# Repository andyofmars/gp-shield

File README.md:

# gp-shield
## A general purpose arduino-compatible shield for UTAS projects

## Overview
The shield is intended to be used as a general purpose shield for Arduino Uno compatible microcontroller development boards or as an interface between a development board and other custom electronics.

From previous projects we have identified multiple common issues when interfacing with common microcontroller development boards including the Arduino UNO and Xplained Mini series of development boards.
- Many development boards are sensitive to fluctuations in the power supply during programming and can become 'bricked'.
- A lack of protection on the Vin and 5V lines when being powered from a shield or other electronics makes them susceptible to damage.
- Due to the lack of protection and the large number of exposed GPIO pins it is easy to draw too much current or apply an overvoltage condition which will damage the microcontroller.

**See [Rugged Circuits](https://www.rugged-circuits.com/10-ways-to-destroy-an-arduino) for more detail on common issues with the Arduino UNO.**

To resolve these issue for most use cases and provide general functionality commonly needed in electronics projects we have developed the gp-shield to be used as the standard method of interfacing with Arduino UNO compatible development boards.

## Features
- Can be powered from external battery (~6V - 20V)
- On-board power supply with overvoltage (25V?), overcurrent (6A), and reverse polarity protection as well as adjustable undervoltage lockout and an on-board or external power switch.
- Onboard 5V regulation (up to 1A output) with circuitry with a jumper to isolate 5V from the development board.
- Overvoltage (~5.1V) and overcurrent (~30mA) protection on all GPIO pins when using the on-board headers and connectors.
- ICD style analogue outputs, PORTD and PORTB GPIO pins, 6 servo-style PWM outputs, UART, SPI and a high current output for powereing other electronics from the same supply with all of the built in seafty features.
- On-board microcontroller reset button
- On-board general purpose LED and push button

The board itself is 2-layers with double-sided load. All components use footprints suitable for hand-soldering. It is intended to be assembled in-house using pick-and-place machine and reflow soldering.

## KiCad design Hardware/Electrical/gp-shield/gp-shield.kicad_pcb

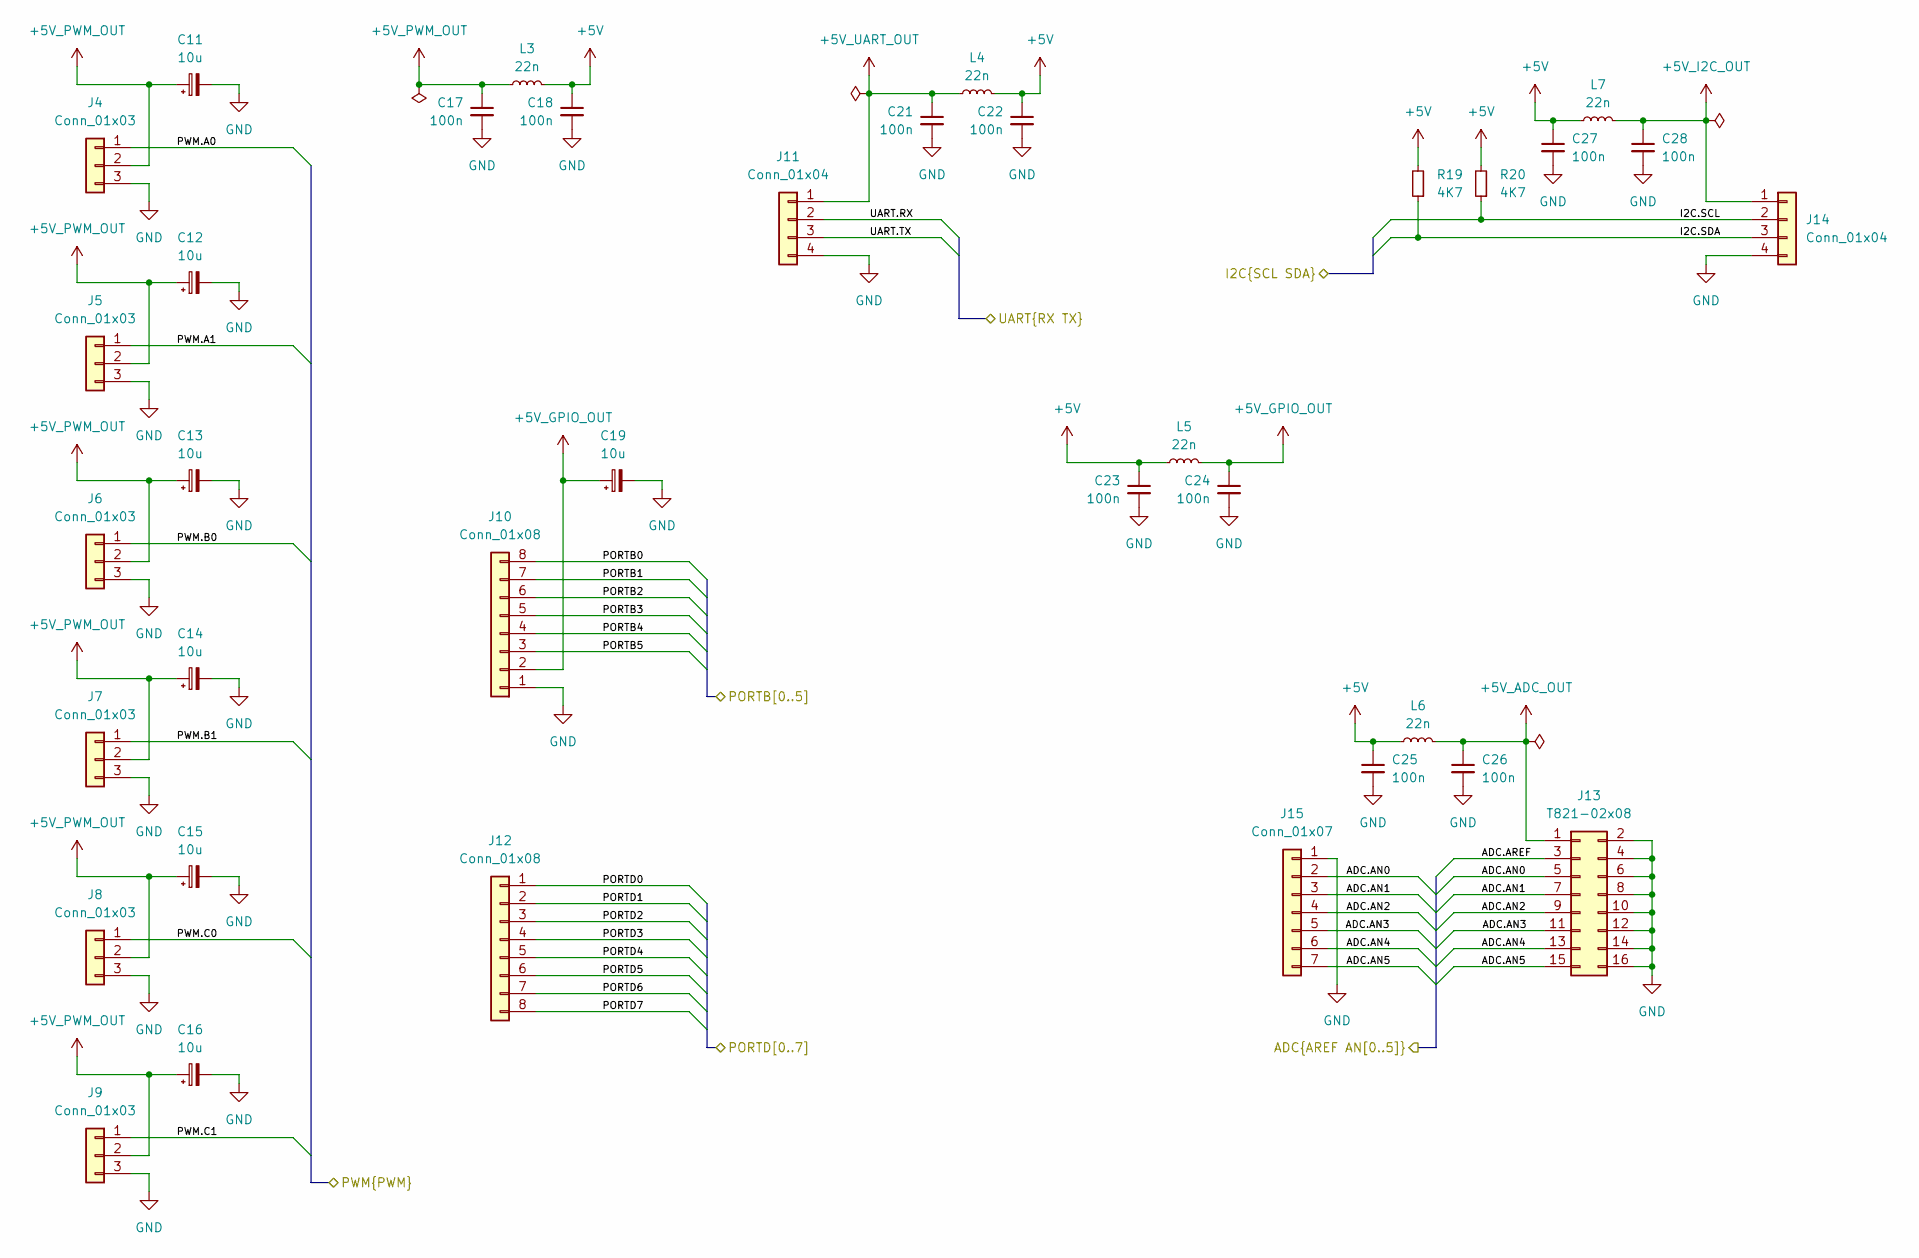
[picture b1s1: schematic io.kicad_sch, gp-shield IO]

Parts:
C11, C12, C13, C14, C15, C16, C19: 10u; C_0805_2012Metric_Pad1.18x1.45mm_HandSolder
C17, C18, C21, C22, C23, C24, C25, C26, C27, C28: 100n; C_0805_2012Metric_Pad1.18x1.45mm_HandSolder
J4, J5, J6, J7, J8, J9: Conn_01x03; PinHeader_1x03_P2.54mm_Vertical
J10, J12: Conn_01x08; PinSocket_1x08_P2.54mm_Vertical
J11, J14: Conn_01x04; Molex_KK-254_AE-6410-04A_1x04_P2.54mm_Vertical
J13: T821-02x08; IDC-Header_2x08_P2.54mm_Horizontal
J15: Conn_01x07; PinSocket_1x07_P2.54mm_Vertical
L3, L4, L5, L6, L7: 22n; L_0805_2012Metric_Pad1.15x1.40mm_HandSolder
R19, R20: 4K7; R_0805_2012Metric_Pad1.20x1.40mm_HandSolder

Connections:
+5V: C18.1, C22.1, C23.1, C25.1, C27.1, L3.1, L4.1, L5.2, L6.1, L7.1, R19.2, R20.2; also elsewhere on the board
+5V_ADC_OUT: C26.1, J13.1, L6.2
+5V_GPIO_OUT: C19.1, C24.1, J10.2, L5.1
+5V_I2C_OUT: C28.1, J14.1, L7.2
+5V_PWM_OUT: C11.1, C12.1, C13.1, C14.1, C15.1, C16.1, C17.1, J4.2, J5.2, J6.2, J7.2, J8.2, J9.2, L3.2
+5V_UART_OUT: C21.1, J11.1, L4.2
/IO/ADC.AN0: J13.5, J15.2; also elsewhere on the board
/IO/ADC.AN1: J13.7, J15.3; also elsewhere on the board
/IO/ADC.AN2: J13.9, J15.4; also elsewhere on the board
/IO/ADC.AN3: J13.11, J15.5; also elsewhere on the board
/IO/ADC.AN4: J13.13, J15.6; also elsewhere on the board
/IO/ADC.AN5: J13.15, J15.7; also elsewhere on the board
/IO/ADC.AREF: J13.3; also elsewhere on the board
/IO/I2C.SCL: J14.2, R20.1; also elsewhere on the board
/IO/I2C.SDA: J14.3, R19.1; also elsewhere on the board
/IO/PORTB0: J10.8; also elsewhere on the board
/IO/PORTB1: J10.7; also elsewhere on the board
/IO/PORTB2: J10.6; also elsewhere on the board
/IO/PORTB3: J10.5; also elsewhere on the board
/IO/PORTB4: J10.4; also elsewhere on the board
/IO/PORTB5: J10.3; also elsewhere on the board
/IO/PORTD0: J12.1; also elsewhere on the board
/IO/PORTD1: J12.2; also elsewhere on the board
/IO/PORTD2: J12.3; also elsewhere on the board
/IO/PORTD3: J12.4; also elsewhere on the board
/IO/PORTD4: J12.5; also elsewhere on the board
/IO/PORTD5: J12.6; also elsewhere on the board
/IO/PORTD6: J12.7; also elsewhere on the board
/IO/PORTD7: J12.8; also elsewhere on the board
/IO/PWM.A0: J4.1; also elsewhere on the board
/IO/PWM.A1: J5.1; also elsewhere on the board
/IO/PWM.B0: J6.1; also elsewhere on the board
/IO/PWM.B1: J7.1; also elsewhere on the board
/IO/PWM.C0: J8.1; also elsewhere on the board
/IO/PWM.C1: J9.1; also elsewhere on the board
/IO/UART.RX: J11.2; also elsewhere on the board
/IO/UART.TX: J11.3; also elsewhere on the board
GND: C11.2, C12.2, C13.2, C14.2, C15.2, C16.2, C17.2, C18.2, C19.2, C21.2, C22.2, C23.2, C24.2, C25.2, C26.2, C27.2, C28.2, J4.3, J5.3, J6.3, J7.3, J8.3, J9.3, J10.1, J11.4, J13.2, J13.4, J13.6, J13.8, J13.10, J13.12, J13.14, J13.16, J14.4, J15.1; also elsewhere on the board

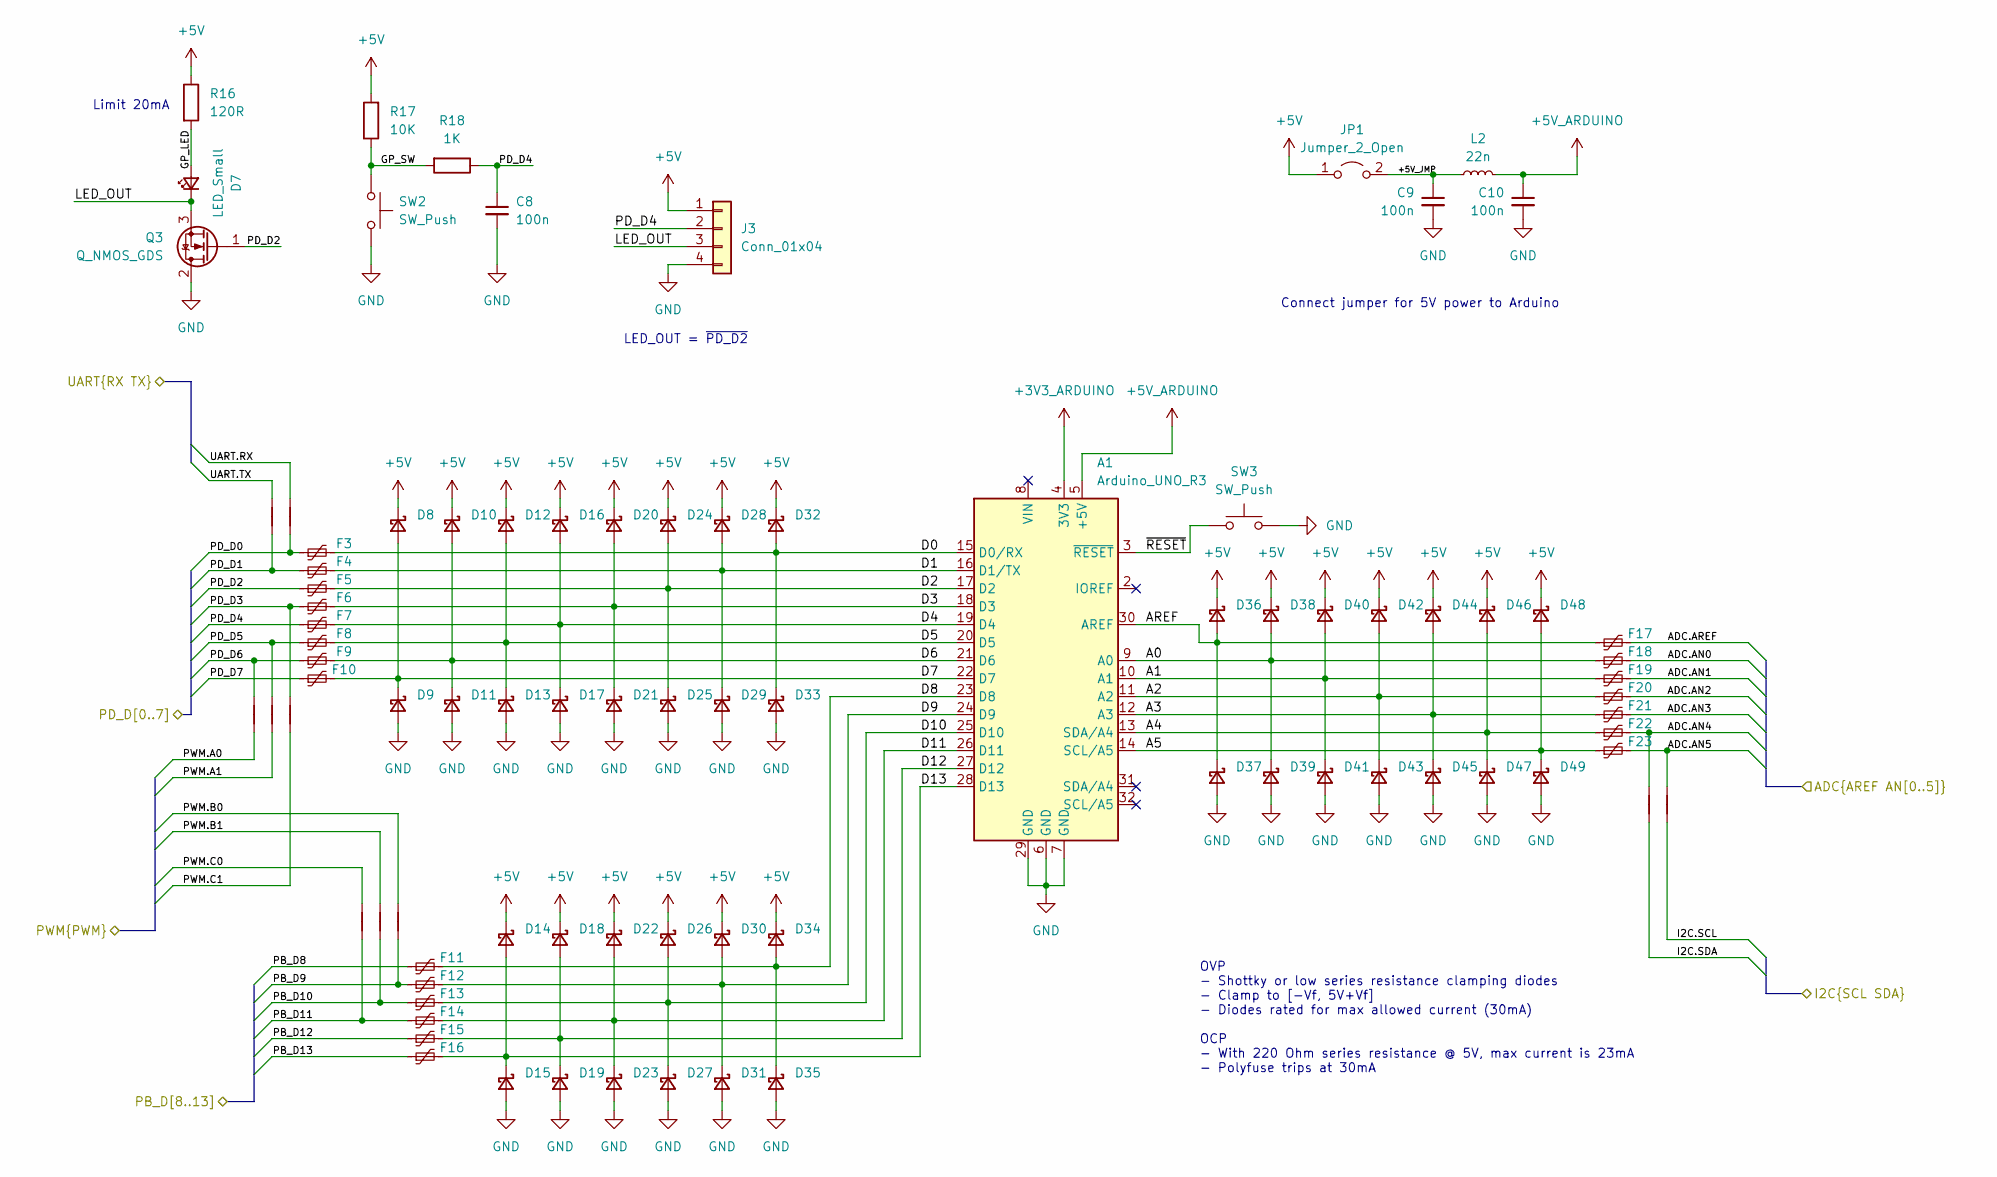
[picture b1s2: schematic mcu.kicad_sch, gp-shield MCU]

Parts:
A1: Arduino_UNO_R3
C8, C9, C10: 100n; C_0805_2012Metric_Pad1.18x1.45mm_HandSolder
D7: LED_Small; LED_0805_2012Metric_Pad1.15x1.40mm_HandSolder
D8, D9, D10, D11, D12, D13, D14, D15, D16, D17, D18, D19, D20, D21, D22, D23, D24, D25, D26, D27, D28, D29, D30, D31, D32, D33, D34, D35, D36, D37, D38, D39, D40, D41, D42, D43, D44, D45, D46, D47, D48, D49: D_Schottky_Small; D_0805_2012Metric_Pad1.15x1.40mm_HandSolder
F3, F4, F5, F6, F7, F8, F9, F10, F11, F12, F13, F14, F15, F16, F17, F18, F19, F20, F21, F22, F23: Polyfuse_Small; Fuse_0805_2012Metric_Pad1.15x1.40mm_HandSolder; Digikey Part No PRG18BB221MB1RB
J3: Conn_01x04; Molex_KK-254_AE-6410-04A_1x04_P2.54mm_Vertical
JP1: Jumper_2_Open; PinHeader_1x02_P2.54mm_Vertical
L2: 22n; L_0805_2012Metric_Pad1.15x1.40mm_HandSolder
NT1, NT2, NT3, NT4, NT5, NT6, NT7, NT8, NT9, NT10: NetTie_2; NetTie-2_THT_Pad0.3mm
Q3: Q_NMOS_GDS; SOT-23
R16: 120R; R_0805_2012Metric_Pad1.20x1.40mm_HandSolder
R17: 10K; R_0805_2012Metric_Pad1.20x1.40mm_HandSolder
R18: 1K; R_0805_2012Metric_Pad1.20x1.40mm_HandSolder
SW2, SW3: SW_Push; SW_TH_Tactile_Omron_B3F-10xx

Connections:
+3V3_ARDUINO: A1.4 (3V3)
+5V: D8.1 (K), D10.1 (K), D12.1 (K), D14.1 (K), D16.1 (K), D18.1 (K), D20.1 (K), D22.1 (K), D24.1 (K), D26.1 (K), D28.1 (K), D30.1 (K), D32.1 (K), D34.1 (K), D36.1 (K), D38.1 (K), D40.1 (K), D42.1 (K), D44.1 (K), D46.1 (K), D48.1 (K), J3.1, JP1.1 (A), R16.1, R17.2; also elsewhere on the board
+5V_ARDUINO: A1.5 (+5V), C10.1, L2.1
/IO/ADC.AN0: F18.2; also elsewhere on the board
/IO/ADC.AN1: F19.2; also elsewhere on the board
/IO/ADC.AN2: F20.2; also elsewhere on the board
/IO/ADC.AN3: F21.2; also elsewhere on the board
/IO/ADC.AN4: F22.2, NT9.2; also elsewhere on the board
/IO/ADC.AN5: F23.2, NT10.2; also elsewhere on the board
/IO/ADC.AREF: F17.2; also elsewhere on the board
/IO/I2C.SCL: NT10.1; also elsewhere on the board
/IO/I2C.SDA: NT9.1; also elsewhere on the board
/IO/PORTB0: F11.1; also elsewhere on the board
/IO/PORTB1: F12.1, NT8.1; also elsewhere on the board
/IO/PORTB2: F13.1, NT7.1; also elsewhere on the board
/IO/PORTB3: F14.1, NT6.1; also elsewhere on the board
/IO/PORTB4: F15.1; also elsewhere on the board
/IO/PORTB5: F16.1; also elsewhere on the board
/IO/PORTD0: F3.1, NT4.1; also elsewhere on the board
/IO/PORTD1: F4.1, NT2.1; also elsewhere on the board
/IO/PORTD2: F5.1, Q3.1 (G); also elsewhere on the board
/IO/PORTD3: F6.1, NT5.2; also elsewhere on the board
/IO/PORTD4: C8.1, F7.1, J3.2, R18.1; also elsewhere on the board
/IO/PORTD5: F8.1, NT3.2; also elsewhere on the board
/IO/PORTD6: F9.1, NT1.2; also elsewhere on the board
/IO/PORTD7: F10.1; also elsewhere on the board
/IO/PWM.A0: NT1.1; also elsewhere on the board
/IO/PWM.A1: NT3.1; also elsewhere on the board
/IO/PWM.B0: NT8.2; also elsewhere on the board
/IO/PWM.B1: NT7.2; also elsewhere on the board
/IO/PWM.C0: NT6.2; also elsewhere on the board
/IO/PWM.C1: NT5.1; also elsewhere on the board
/IO/UART.RX: NT4.2; also elsewhere on the board
/IO/UART.TX: NT2.2; also elsewhere on the board
/MCU/+5V_JMP: C9.1, JP1.2 (B), L2.2
/MCU/A0: A1.9 (A0), D38.2 (A), D39.1 (K), F18.1
/MCU/A1: A1.10 (A1), D40.2 (A), D41.1 (K), F19.1
/MCU/A2: A1.11 (A2), D42.2 (A), D43.1 (K), F20.1
/MCU/A3: A1.12 (A3), D44.2 (A), D45.1 (K), F21.1
/MCU/A4: A1.13 (SDA/A4), D46.2 (A), D47.1 (K), F22.1
/MCU/A5: A1.14 (SCL/A5), D48.2 (A), D49.1 (K), F23.1
/MCU/AREF: A1.30 (AREF), D36.2 (A), D37.1 (K), F17.1
/MCU/D0: A1.15 (D0/RX), D32.2 (A), D33.1 (K), F3.2
/MCU/D1: A1.16 (D1/TX), D28.2 (A), D29.1 (K), F4.2
/MCU/D2: A1.17 (D2), D24.2 (A), D25.1 (K), F5.2
/MCU/D3: A1.18 (D3), D20.2 (A), D21.1 (K), F6.2
/MCU/D4: A1.19 (D4), D16.2 (A), D17.1 (K), F7.2
/MCU/D5: A1.20 (D5), D12.2 (A), D13.1 (K), F8.2
/MCU/D6: A1.21 (D6), D10.2 (A), D11.1 (K), F9.2
/MCU/D7: A1.22 (D7), D8.2 (A), D9.1 (K), F10.2
/MCU/D8: A1.23 (D8), D34.2 (A), D35.1 (K), F11.2
/MCU/D9: A1.24 (D9), D30.2 (A), D31.1 (K), F12.2
/MCU/D10: A1.25 (D10), D26.2 (A), D27.1 (K), F13.2
/MCU/D11: A1.26 (D11), D22.2 (A), D23.1 (K), F14.2
/MCU/D12: A1.27 (D12), D18.2 (A), D19.1 (K), F15.2
/MCU/D13: A1.28 (D13), D14.2 (A), D15.1 (K), F16.2
/MCU/GP_LED: D7.2 (A), R16.2
/MCU/GP_SW: R17.1, R18.2, SW2.1
/MCU/LED_OUT: D7.1 (K), J3.3, Q3.3 (S)
/MCU/~RESET: A1.3 (~RESET), SW3.1
GND: A1.6 (GND), A1.7 (GND), A1.29 (GND), C8.2, C9.2, C10.2, D9.2 (A), D11.2 (A), D13.2 (A), D15.2 (A), D17.2 (A), D19.2 (A), D21.2 (A), D23.2 (A), D25.2 (A), D27.2 (A), D29.2 (A), D31.2 (A), D33.2 (A), D35.2 (A), D37.2 (A), D39.2 (A), D41.2 (A), D43.2 (A), D45.2 (A), D47.2 (A), D49.2 (A), J3.4, Q3.2 (D), SW2.2, SW3.2; also elsewhere on the board

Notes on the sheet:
LED_OUT = ~{PD_D2}
OVP - Shottky or low series resistance clamping diodes - Clamp to [-Vf, 5V+Vf] - Diodes rated for max allowed current (30mA) OCP - With 220 Ohm series resistance @ 5V, max current is 23mA - Polyfuse trips at 30mA
Limit 20mA
Connect jumper for 5V power to Arduino

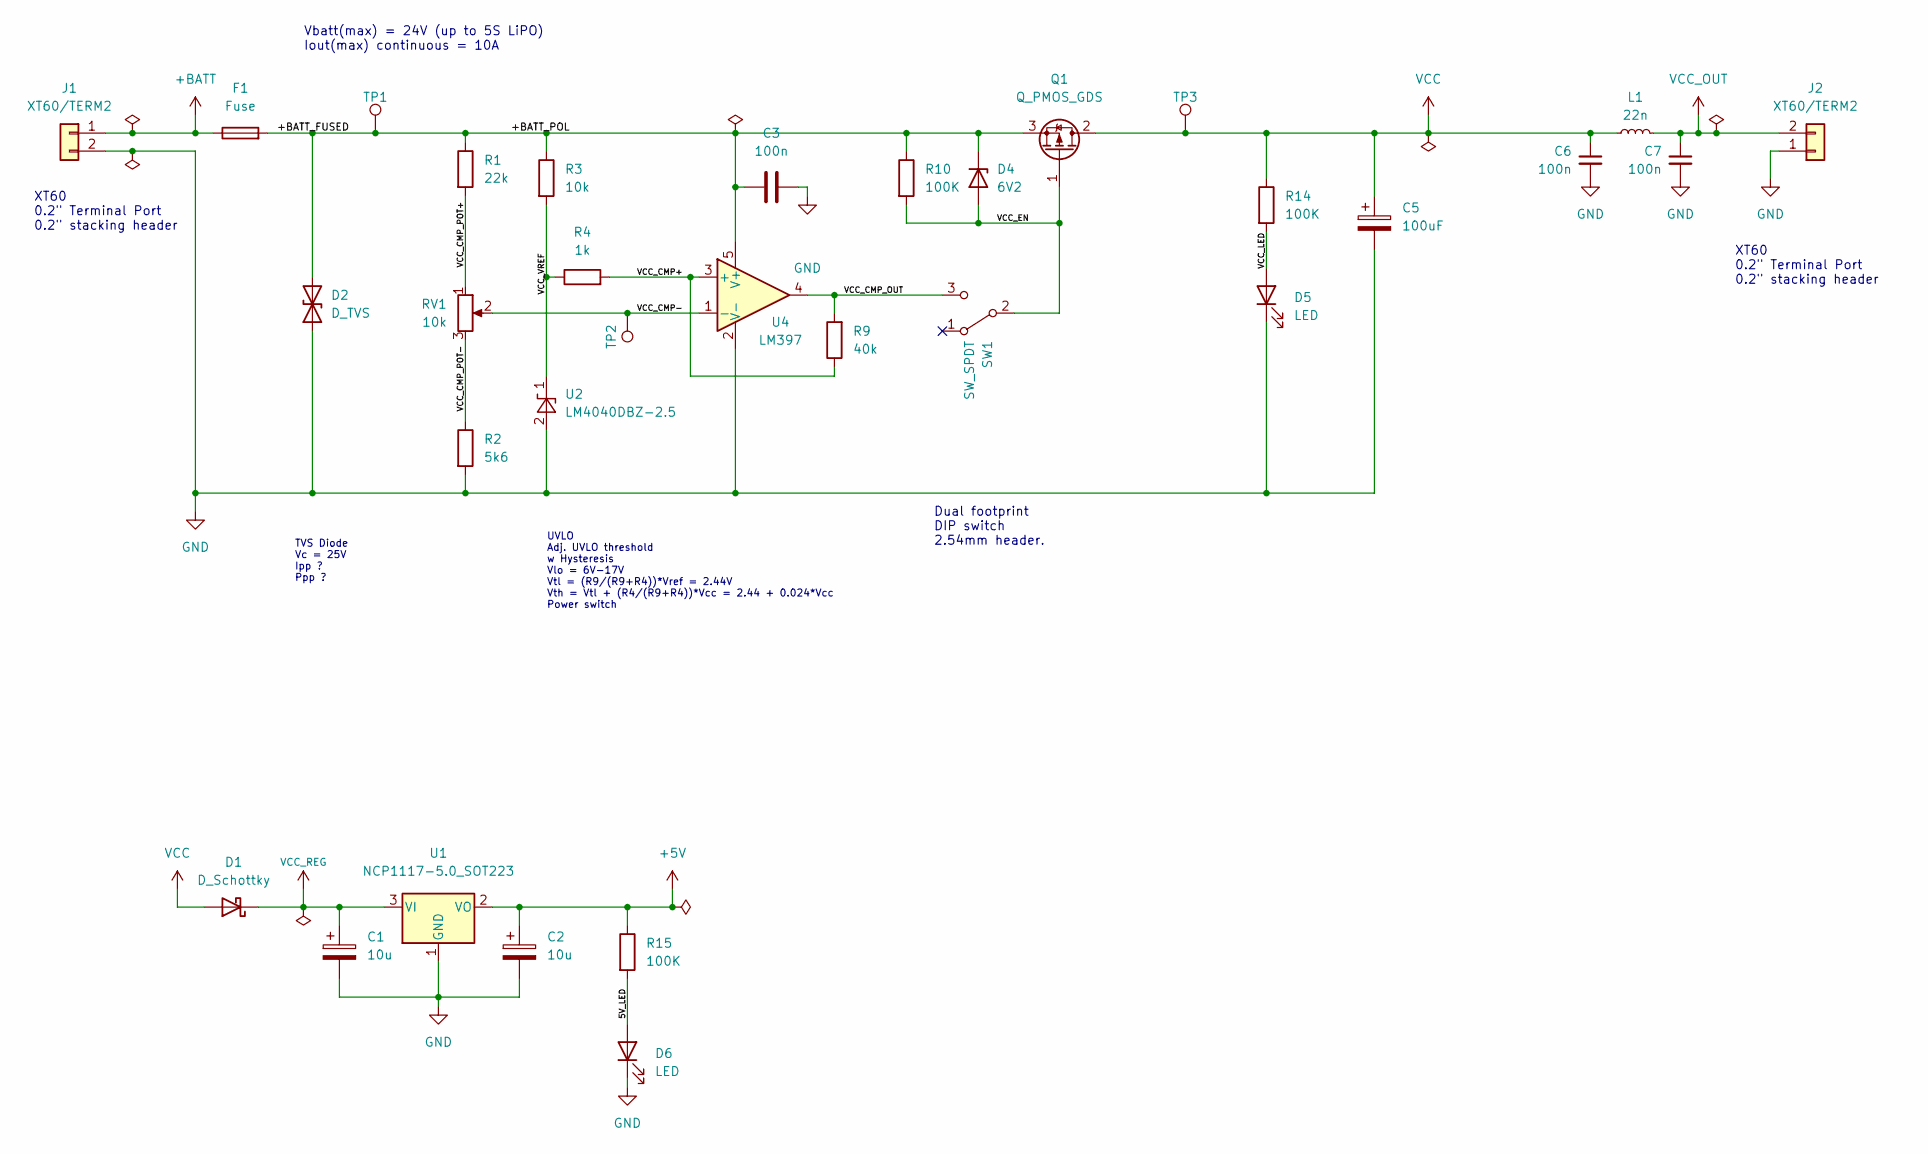
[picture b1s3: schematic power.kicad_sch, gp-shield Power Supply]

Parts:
C1, C2: 10u; C_0805_2012Metric_Pad1.18x1.45mm_HandSolder
C3, C6, C7: 100n; C_0805_2012Metric_Pad1.18x1.45mm_HandSolder
C5: 100uF; CP_Radial_D8.0mm_P3.50mm
D1: D_Schottky; D_0805_2012Metric_Pad1.15x1.40mm_HandSolder
D2: D_TVS; D_SMA
D4: 6V2; D_0805_2012Metric_Pad1.15x1.40mm_HandSolder
D5, D6: LED; LED_0805_2012Metric_Pad1.15x1.40mm_HandSolder
F1: Fuse; Fuseholder_Littelfuse_445_030_series_5x20mm
J1, J2: XT60/TERM2; Combined_TerminalBlock_5.08_XT60_2Row0.2Header
L1: 22n; L_0805_2012Metric_Pad1.15x1.40mm_HandSolder
Q1: Q_PMOS_GDS; TO-252-3_TabPin2
R1: 22k; R_0805_2012Metric_Pad1.20x1.40mm_HandSolder
R2: 5k6; R_0805_2012Metric_Pad1.20x1.40mm_HandSolder
R3: 10k; R_0805_2012Metric_Pad1.20x1.40mm_HandSolder
R4: 1k; R_0805_2012Metric_Pad1.20x1.40mm_HandSolder
R9: 40k; R_0805_2012Metric_Pad1.20x1.40mm_HandSolder
R10, R14, R15: 100K; R_0805_2012Metric_Pad1.20x1.40mm_HandSolder
RV1: 10k; Potentiometer_Bourns_3214W_Vertical
SW1: SW_SPDT; OS102011MA1_SPDT_ESwitch
TP1, TP2, TP3: TestPoint; TestPoint_THTPad_D2.0mm_Drill1.0mm
U1: NCP1117-5.0_SOT223; SOT-223-3_TabPin2
U2: LM4040DBZ-2.5; SOT-23
U4: LM397; SOT-23-5

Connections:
+5V: C2.1, R15.1, U1.2 (VO); also elsewhere on the board
+BATT: F1.1, J1.1
/Power/5V_LED: D6.2 (A), R15.2
/Power/+BATT_FUSED: C3.1, D2.2 (A2), D4.1 (K), F1.2, Q1.3 (S), R1.1, R3.1, R10.1, TP1.1, U4.5 (V+)
/Power/VCC_CMP+: R4.2, R9.1, U4.3 (+)
/Power/VCC_CMP-: RV1.2, TP2.1, U4.1 (-)
/Power/VCC_CMP_OUT: R9.2, SW1.3 (C), U4.4
/Power/VCC_CMP_POT+: R1.2, RV1.1
/Power/VCC_CMP_POT-: R2.1, RV1.3
/Power/VCC_EN: D4.2 (A), Q1.1 (G), R10.2, SW1.2 (B)
/Power/VCC_LED: D5.2 (A), R14.2
/Power/VCC_VREF: R3.2, R4.1, U2.1 (K)
GND: C1.2, C2.2, C3.2, C5.2, C6.2, C7.2, D2.1 (A1), D5.1 (K), D6.1 (K), J1.2, J2.1, R2.2, U1.1 (GND), U2.2 (A), U4.2 (V-); also elsewhere on the board
VCC: C5.1, C6.1, D1.2 (A), L1.2, Q1.2 (D), R14.1, TP3.1
VCC_OUT: C7.1, J2.2, L1.1
VCC_REG: C1.1, D1.1 (K), U1.3 (VI)

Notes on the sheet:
XT60 0.2" Terminal Port 0.2" stacking header
Dual footprint DIP switch 2.54mm header.
UVLO Adj. UVLO threshold w Hysteresis Vlo = 6V-17V Vtl = (R9/(R9+R4))*Vref = 2.44V Vth = Vtl + (R4/(R9+R4))*Vcc = 2.44 + 0.024*Vcc Power switch
Vbatt(max) = 24V (up to 5S LiPO) Iout(max) continuous = 10A
TVS Diode Vc = 25V Ipp ? Ppp ?

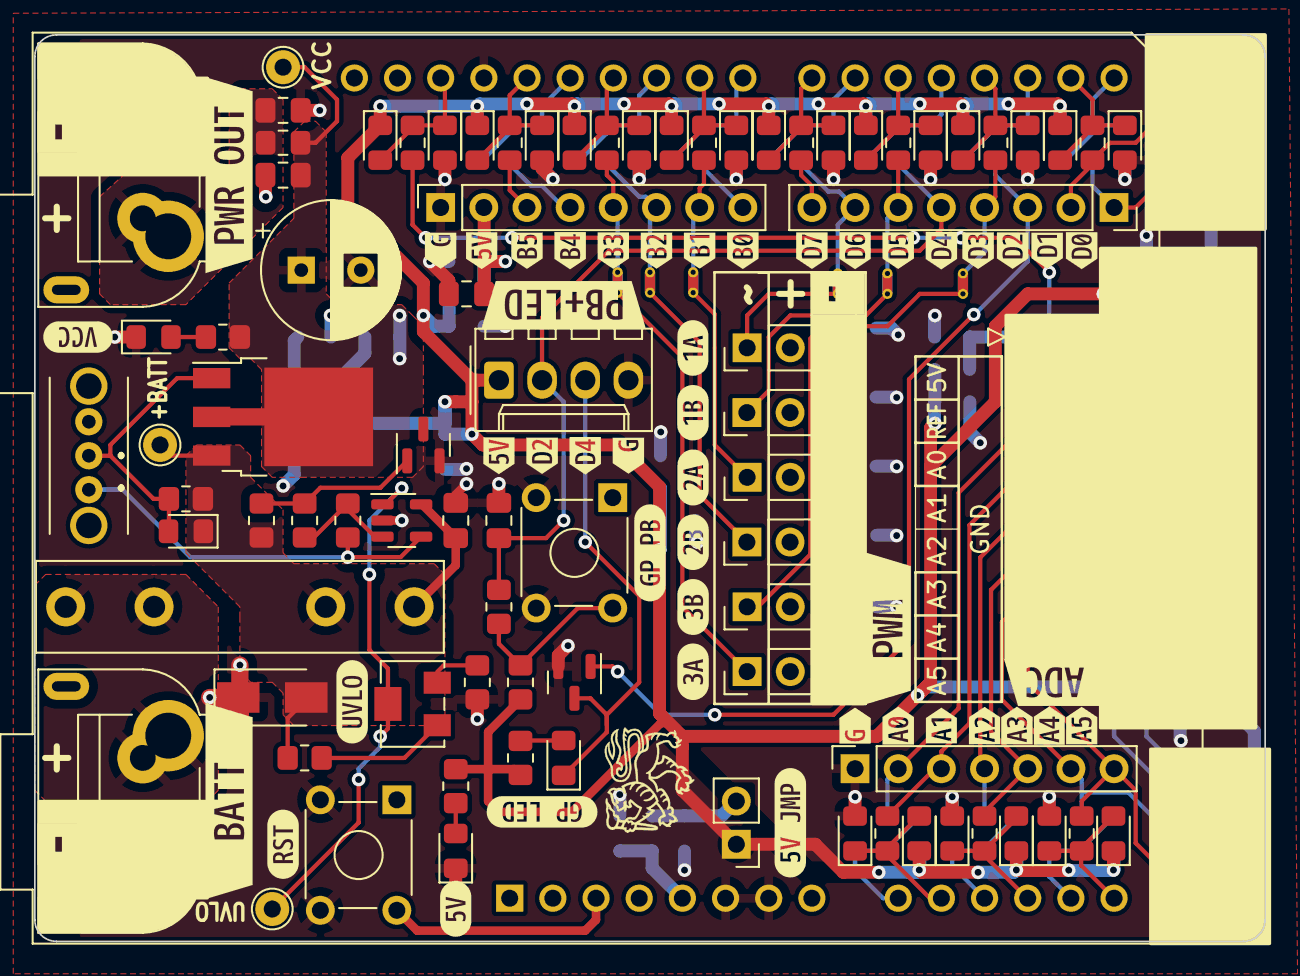
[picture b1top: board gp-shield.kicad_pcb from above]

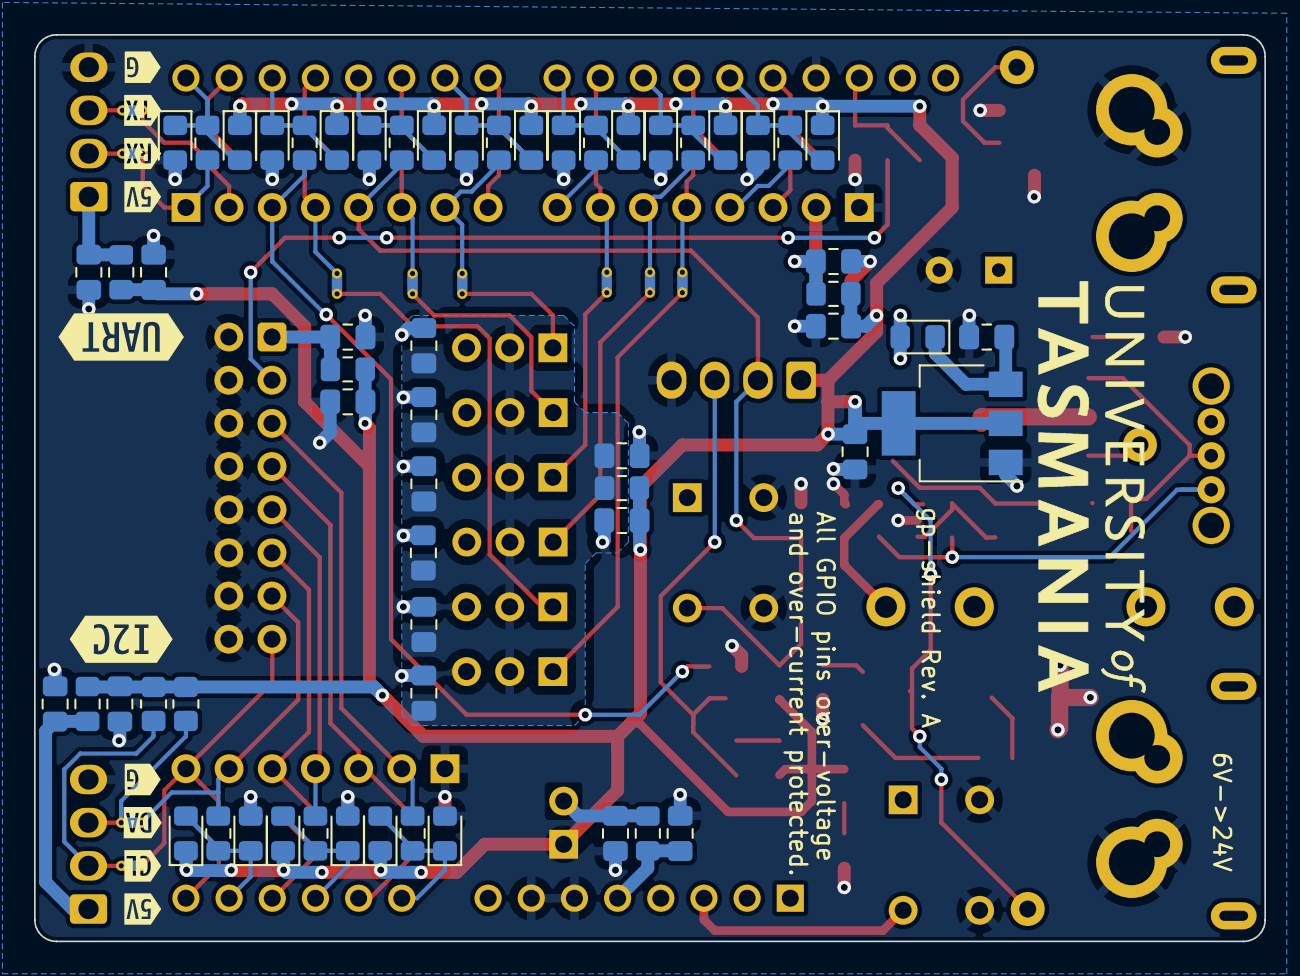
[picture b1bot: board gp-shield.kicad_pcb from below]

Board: 2 copper layers, 72.4 x 53.3 mm, 213 parts (71 on the bottom side), 79 nets.

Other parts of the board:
kibuzzard-636B2D3F: G***; kibuzzard-636B2D3F
kibuzzard-636B3B8D: G***; kibuzzard-636B3B8D
kibuzzard-636B3BDA: G***; kibuzzard-636B3BDA
kibuzzard-636B3BFE: G***; kibuzzard-636B3BFE
kibuzzard-636B3C0D: G***; kibuzzard-636B3C0D
kibuzzard-636B3C1B: G***; kibuzzard-636B3C1B
kibuzzard-636B3C06: G***; kibuzzard-636B3C06
kibuzzard-636B3C14: G***; kibuzzard-636B3C14
kibuzzard-636B3C68: G***; kibuzzard-636B3C68
kibuzzard-636B3D37: G***; kibuzzard-636B3D37
kibuzzard-636B29B0: G***; kibuzzard-636B29B0
kibuzzard-636B29F7: G***; kibuzzard-636B29F7
kibuzzard-636B37C6: G***; kibuzzard-636B37C6
kibuzzard-636B37CC: G***; kibuzzard-636B37CC
kibuzzard-636B37D3: G***; kibuzzard-636B37D3
kibuzzard-636B37D9: G***; kibuzzard-636B37D9
kibuzzard-636B37E0: G***; kibuzzard-636B37E0
kibuzzard-636B37FB: G***; kibuzzard-636B37FB
kibuzzard-636B38AF: G***; kibuzzard-636B38AF
kibuzzard-636B41C3: G***; kibuzzard-636B41C3
kibuzzard-636B290E: G***; kibuzzard-636B290E
kibuzzard-636B388A: G***; kibuzzard-636B388A
kibuzzard-636B437B: G***; kibuzzard-636B437B
kibuzzard-636B2900: G***; kibuzzard-636B2900
kibuzzard-636B3819: G***; kibuzzard-636B3819
kibuzzard-636B3822: G***; kibuzzard-636B3822
kibuzzard-636B3829: G***; kibuzzard-636B3829
kibuzzard-636B3831: G***; kibuzzard-636B3831
kibuzzard-636B3838: G***; kibuzzard-636B3838
kibuzzard-636B3843: G***; kibuzzard-636B3843
kibuzzard-636B3849: G***; kibuzzard-636B3849
kibuzzard-636B3891: G***; kibuzzard-636B3891
kibuzzard-636C5C0D: G***; kibuzzard-636C5C0D
kibuzzard-636C5C1C: G***; kibuzzard-636C5C1C
kibuzzard-636C5C4A: G***; kibuzzard-636C5C4A
kibuzzard-636C5C28: G***; kibuzzard-636C5C28
kibuzzard-636C5C36: G***; kibuzzard-636C5C36
kibuzzard-636C5C55: G***; kibuzzard-636C5C55
kibuzzard-636C5C62: G***; kibuzzard-636C5C62
kibuzzard-636C5C70: G***; kibuzzard-636C5C70
kibuzzard-636C54A9: G***; kibuzzard-636C54A9
kibuzzard-636C5470: G***; kibuzzard-636C5470
kibuzzard-63524FB6: G***; kibuzzard-63524FB6
kibuzzard-63524FC9: G***; kibuzzard-63524FC9
kibuzzard-63527D9E: G***; kibuzzard-63527D9E
kibuzzard-63527D35: G***; kibuzzard-63527D35
kibuzzard-63527DAD: G***; kibuzzard-63527DAD
kibuzzard-635273D0: G***; kibuzzard-635273D0
kibuzzard-635273DC: G***; kibuzzard-635273DC
kibuzzard-6352498A: G***; kibuzzard-6352498A
kibuzzard-6352739F: G***; kibuzzard-6352739F
kibuzzard-63524950: G***; kibuzzard-63524950
kibuzzard-63524966: G***; kibuzzard-63524966
kibuzzard-63524973: G***; kibuzzard-63524973
kibuzzard-63524980: G***; kibuzzard-63524980
kibuzzard-63524994: G***; kibuzzard-63524994
kibuzzard-63527359: G***; kibuzzard-63527359
kibuzzard-63527364: G***; kibuzzard-63527364

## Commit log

2022-10-20 Added PWM connectors, subnet labels, arduino power supply protection
2022-10-22 Major revisions to PCB layout
    - near final layout
    - prototype version of silkscreen
    - removed 3.3V reg
2022-10-23 Added net classes
2022-10-27 Added spice models of power supply
    5v-reg in progress
2022-10-27 Updated PCB
    - changed switch footprint
    - created footprint library for E switch varieties
2022-10-27 Updated Power supply design
    Simplified reverse polarity and overvoltage protection
    Added adjustable UVLO with precision Vref
    Added hysteresis to comparators
    Added precision reference to 5V cmp circuit.
2022-10-27 Added clamping diodes
    Replaced zener regulator protection for GPIO with bidierectional schottky clamping diodes
2022-11-03 Major revisions
2022-11-03 Changes to component footprints
2022-11-09 Major PCB changes
    Added combined footprint for XT60 and terminal port.
    Fixed polarity of Batt and PWR_out connectors.
    Standardised polarity markers to show negative on white.
    Moved Port D and Port B connectors to be inline with existing arduino connectors. Removed extra pins.
    Added analogue in-line output.
    Adjusted component placement for more space around power supply and GP PB and LED.
2022-11-10 Complete draft PCB layout
    Added updated renders to doc.
    Added some documentation to schematic
    complete PCB layout with some revisions still needed
2022-11-10 Minor changes to silkscreen and documentation
2022-11-10 Added small radius to board edges
2022-11-10 Additional 3d models
2022-11-10 Added symbol and footprint for gp-shield headers
2022-11-24 Updated footprints and PCB layout
    Updated reverse polarity and overvoltage to use bidirectional TVS diode
    Changed footprint of TVS diode
    Changed footprint of fuse to proper 5x20mm fuse holder
    Changed footprint of PMOS high side switch to DPAK
    Updated layout with Vreg on backside
2022-12-01 Changes to board setup and rules
    Changed to White soldermask with Black silkscreen.
    Tweaked Terminal port dual footprint
    Adjusted rules for courtyard clearance
2022-12-01 Removed net ties from BOM
2022-12-01 Minor cosmetic imporvements
    title block and colour theme
2022-12-02 Minor tweaks to annotation
2023-02-24 Added test points for key power signals
2023-02-24 merged test point changes
2023-02-24 Minor annotation fixes from merge
2023-03-17 Minor changes to annotation and silkscreen
